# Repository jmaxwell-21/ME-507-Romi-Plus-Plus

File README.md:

# ME 507 Romi++ Project

Design repository for Romi++, a self-balancing differential drive robot developed for Cal Poly's ME 507 Mechanical Control Systems Design class.

## Documentation

[View the complete Doxygen code documentation](https://jmaxwell-21.github.io/ME-507-Romi-Plus-Plus/)

## GitHub File Structure

- `Firmware/` - STM32CubeIDE project source code and FSM diagrams
- `Hardware/` - Mechanical and electrical design files and information
- `Media/` -  Project photos and videos
- `docs/` - Doxygen-generated HTML documentation

---

Made by Jack Maxwell  
Cal Poly | Spring 2025

# Overview

Romi++ is a two-wheeled differential drive robot with a cylindrical body. It can be remotely controlled by either a computer or the custom [Smart Knob Controller](https://github.com/Larson-Nick/SmartKnobController) built by my partner and can drive at speeds up to 1&nbsp;m/s while autonomously maintaining balance through PID control.

## See Romi++ in action!
<table>
  <tr>
    <td align="center" valign="top">
      <a href="https://youtube.com/shorts/c_1nM_AD648">
        <br>
        <strong>Official Project Demo</strong>
      </a>
      <p>Official project demo showcasing wireless two-wheeled robot with custom controller (using attachments before balance control was implemented).</p>
    </td>
    <td align="center" valign="top">
      <a href="https://youtube.com/shorts/LBDbpKdLq8A">
        <br>
        <strong>Bonus Project Demo</strong>
      </a>
      <p>Final demo with balance control enabled, allowing the robot to stay level while driving without attachments.</p>
    </td>
  </tr>
</table>

This project serves as a successor to my [Romi Line-Following Robot](https://github.com/finite-colin-machine/ME-405-Romi) project from ME 405 at Cal Poly. Unlike the original Romi, which used caster wheels for stability, Romi++ is cylindrical and free to rotate about its drive axis, requiring active balance control to remain upright.

Romi++ was my term project for the ME 507 Mechanical Control Systems Design class at Cal Poly. It was a perfect blend of the four core areas of mechatronics: mechanical design, electronics, embedded systems, and control systems. These aspects of my project are explained in more depth below.

## Mechanical Design

The main components of the robot are the 3D-printed cylindrical body, two motors with wheels, a battery compartment, and various fasteners. The motors are mounted beneath the mounting plate and screw into the cylinder sides. The battery sits in a small box beneath the mounting plate, while the electronics rest on top. Long standoffs connect both cylinder halves to the mounting plate.

All 3D-printed components were custom designed, while purchased components (motors, wheels, battery, fasteners) were integrated into the assembly. The challenge was ensuring proper fitment and mounting points for each component. I imported vendor-supplied CAD models into SolidWorks and iteratively refined the design to accommodate all components with appropriate mounting holes and clearances.

See the [Mechanical Design](Hardware/Mechanical) folder for more information on specific components.

## Electrical Design

The PCB that I designed for Romi++ was my first experience with electronics design. It took up a significant portion of the 10-week course, but it was worth it for all of the experience I gained (and the fun I had)!

The PCB has 9 main components: the power distribution system to supply various voltage levels to the system, the STM32 microcontroller to control all the components, an IMU to measure heading and pitch, 2 drivers and pin headers for the motors, a pin header for the HC-05 Bluetooth module, a pin header for the ST-Link debugger, a reset button, and a general-purpose user button. I designed the [schematic](Hardware/Electrical/PCB%20Schematic.pdf) and board layout in Fusion 360 and had it manufactured by JLCPCB.

See the [Electrical Design](Hardware/Electrical) folder for complete schematics, board layouts, and manufacturing files.

### Power Distribution

The robot is powered by a 3S LiPo battery with a nominal voltage of 11.1&nbsp;V. A [fuse](https://www.digikey.com/en/products/detail/littelfuse-inc/2920l400-15mr/6234817) and a [p-channel MOSFET](https://www.digikey.com/en/products/detail/infineon-technologies/IRF7416TRPBF/856470) are used for circuit protection, and the 11.1&nbsp;V from the battery goes to the two [motor driver](https://www.digikey.com/en/products/detail/texas-instruments/DRV8231DDAR/16184249) integrated circuits. A [buck regulator](https://www.digikey.com/en/products/detail/texas-instruments/lmr54406fdbvr/15926505) is used to drop the 11.1&nbsp;V to 5&nbsp;V and provide a smooth output for the encoders and the [HC-05](https://www.electronicwings.com/sensors-modules/bluetooth-module-hc-05-), and an [LDO regulator](https://www.digikey.com/en/products/detail/texas-instruments/TPS7A2033PDBVR/13566866?s=N4IgTCBcDaICoAUDKB2AgmADAZmwgIgEIBqASiALoC%2BQA) is used to drop the 5&nbsp;V to 3.3&nbsp;V to power the remaining integrated circuits.

### Microcontroller (MCU)

To run my code and control each peripheral, an [STM32F411CEU6 Microcontroller](https://www.digikey.com/en/products/detail/stmicroelectronics/STM32F411CEU6/4935720) is used. This 32-bit ARM Cortex-M4 MCU running at 100&nbsp;MHz provides sufficient processing power for real-time control loops while offering the necessary peripherals: I2C for the IMU, UART for Bluetooth communication, PWM timers for motor control, and encoder inputs for wheel speed measurement.

### Inertial Measurement Unit (IMU)

To provide heading (yaw) and pitch measurements for the robot's control system, the [BNO055](https://www.digikey.com/en/products/detail/bosch-sensortec/BNO055/6136301) 9-axis absolute orientation sensor is used. The heading data enables precise turning control, while the pitch angle is used by the balance controller to keep the robot upright. Communication with the microcontroller occurs over I2C, with the sensor providing orientation data at up to 100&nbsp;Hz for responsive control.

## Firmware and Controls

The firmware for Romi++ was developed in C/C++ using STM32CubeIDE. While driver implementations can be found in the [Firmware](Firmware) folder, this section focuses on the cooperative multitasking structure and Finite State Machine (FSM) control algorithms that enable the robot's movement.

The firmware uses a pseudo-cooperative multitasking framework where tasks execute sequentially in the main loop. Based on the connected controller (laptop or Smart Knob), different control tasks run in order, each completing its work before passing control to the next task.

### Bluetooth Task

When a laptop is connected, the Bluetooth task runs and decodes signals sent by the [robot controller](Firmware/Additional%20Code/Robot%20Controller.py) Python script. Based on which key is pressed, the task transitions between states that command the motors to move forward, backward, left, or right. When no keys are pressed, it returns to the STOP state. This control interface was primarily used for solo testing, while the custom controller served as the main input method.

### Balance Task

When a laptop is connected, the Balance task reads the pitch angle from the IMU and applies balance control to keep the robot upright. Because the robot is free to rotate about its drive axis, the cylindrical body tilts when the motors spin in the same direction. Without active balance control, the robot cannot drive effectively.

A PID controller compares the current pitch angle to the setpoint (0 degrees) and outputs a corrective motor effort that gets sent to the motor task. This creates a feedback loop that continuously adjusts the motors to maintain balance while driving.

The balance control toggles between IDLE and RUN states when the user button on the PCB is pressed. This allows demonstration of the robot's behavior with and without balance control enabled.

Balance control was not implemented in time for the official project demonstration, which is why an attachment was used to prevent the robot from spinning in that demo. This is also why balance control only runs while a laptop is connected and not with the Smart Knob Controller.

### Parser Task

The Parser task decodes command strings received from the Smart Knob Controller via UART IDLE-line detection with DMA reception. Commands begin with a mode character ('A', 'B', 'C', or 'D') followed by hexadecimal values for motor duty cycles or heading setpoints. The parser extracts these values and makes them available to the motor and heading control tasks.

**Supported modes:**
- **Mode A/B**: Direct motor control (M1 and M2 duty cycles)
- **Mode C**: Reserved for future use
- **Mode D**: Combined heading and motor effort control

### Heading Task

When Mode D is active (combined heading and motor control from the Smart Knob Controller), the Heading task reads the yaw angle from the IMU and controls the robot's orientation. The task tracks the robot's angular position by accumulating angle changes while handling 360-degree wraparound, creating a continuous heading reference.

A PID controller compares the current heading to the commanded setpoint and generates opposing motor efforts for differential steering. These efforts are added to any forward/backward motion commands, allowing the robot to drive while maintaining orientation.

The heading control activates only in Mode D and returns to IDLE when the controller switches modes. Pressing the user button calibrates the heading by resetting the accumulated position to match the current setpoint, which is useful for correcting drift or realigning the reference frame during operation.

### Motor Task

The Motor task serves as the central control hub that integrates commands from all other tasks and translates them into PWM signals for the motor drivers. It receives speed setpoints from either the Bluetooth or Parser tasks and uses encoder feedback to implement closed-loop speed control with PID.

The task continuously reads encoder speeds and calculates PID corrections to match the commanded wheel velocities. Crucially, it then superposes control efforts from the Heading and Balance tasks onto these base speed commands. This allows the robot to simultaneously drive at a target speed, maintain orientation, and stay upright.

The motor task transitions from IDLE to RUN whenever any input source provides non-zero commands or control efforts. Final motor efforts are clamped to safe PWM limits before being sent to the motor drivers, ensuring the robot operates within hardware constraints. This architecture makes the Motor task the final stage in a layered control system where multiple independent controllers work together to achieve complex behavior.

### Battery Check Task

The Battery Check task monitors the battery voltage through an ADC input and provides a visual warning when power drops too low. It continuously reads the analog voltage level and compares it against threshold values to protect the LiPo battery from over-discharge.

When the battery voltage drops below approximately 10.05 V (ADC value < 3300), the task activates an LED indicator and transitions to the BATTERY_LOW state. Once in this state, the LED remains on until the voltage recovers to at least 10.20 V (ADC value > 3350), at which point it turns off and returns to normal monitoring.

This design prevents the LED from flickering on and off when the battery voltage hovers near the threshold, as motor loads can cause temporary voltage dips that recover quickly. When the battery is depleted and requires charging, it must be disconnected to do so. The specific voltage thresholds are chosen to provide a safe margin above the 3 V per cell over-discharge limit (9 V total for a 3S battery).

## Project Results and Reflection

Romi++ successfully demonstrates the integration of mechanical design, electronics, embedded systems, and control systems into a fully functional balancing robot. The final system achieves autonomous balance control, precise heading tracking, and wireless operation through two independent control interfaces.

**Key achievements:**
- DFMA-driven design with standardized fasteners and single-tool access
- Custom PCB design and fabrication with successful implementation
- Multi-layered control architecture with superposed PID controllers
- Wireless control via Bluetooth for laptop and custom controller interfaces

**Challenges and lessons learned:**

Designing the PCB was a grueling task, especially with no prior experience. Over about 4 weeks, I learned about decoupling capacitors, ground planes, trace routing, and many more topics while iterating and improving my design. The end result was a board with no defects that worked perfectly on the first try, which is something I am very proud of!

With only 3 weeks to write and test the code after receiving the PCB, the project required careful prioritization of features. Before implementing balance control, I first had to ensure my robot could communicate with the Smart Knob Controller and interpret its commands for the project demo. Tuning multiple PID controllers required systematic testing documented in the [project videos](Media).

**Future improvements:**
- Enable Bluetooth connection with Xbox/PlayStation controller for more versatile and intuitive control
- Optimize PID gains for faster response and better disturbance rejection
- Create a new iteration with omnidirectional movement, jumping capabilities, and a built-in camera, similar to the [drones in Rainbow Six Siege](https://rainbowsix.fandom.com/wiki/Drone)

This project provided hands-on experience across the full mechatronics design cycle, from initial CAD modeling through PCB design to firmware development and control system tuning. Special thanks to [Nick Larson](https://github.com/Larson-Nick) for developing the Smart Knob Controller that elevated this project's user experience.

## Media Gallery
Check out the [Media folder](Media) for photos and videos of project development. Watch the [full video playlist](https://www.youtube.com/playlist?list=PLDFOiaVsUKKqYprYMNDaC-OZPWteVwOPU) to see the robot's development from first tests to final demonstration.

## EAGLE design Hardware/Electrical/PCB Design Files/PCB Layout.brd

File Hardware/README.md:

# Hardware

This folder contains all electrical and mechanical design files for the Romi++ Differential Drive Robot, including PCB schematics, board layout, manufacturing assets, and CAD models.

## Contents

### `Electrical/` – Fusion PCB design files, manufacturing exports, and board reference images

- `JLCPCB Order Info/` – Gerber files, bill of materials (BOM), and pick-and-place data for PCB fabrication, see notes for more info
- `PCB Design Files/` – Schematic (`.sch`), board layout (`.brd`), 3D model (`.step`), and full Fusion 360 project archive (`.f3z`)
- Additional Files – Reference images of the board, schematic and layout PDFs

### `Mechanical/` – SolidWorks CAD files, 3D-printable models, and robot images

- `SolidWorks 2024 Part Files/` – Native `.SLDPRT` and `.SLDASM` files, including McMaster-Carr fasteners and vendor-supplied STEP models
- `STL 3-D Print Files/` – Exported `.stl` files ready for 3D printing
- `Robot BOM.csv` - Bill of materials for the mechanical assembly, see notes for more info
- Additional Files – Images of the assembled robot and CAD assembly

---

## How to Open the Files

### SolidWorks Files

1. Launch **SolidWorks 2024** or compatible version
2. Open `.SLDASM` files from `SolidWorks 2024 Part Files/`
3. Make sure subfolders (e.g., fasteners, STEP parts) are in the same root for proper assembly resolution

### Fusion 360 Files

1. Open Fusion 360
2. Go to **File → Open**
3. Select `ME 507 Romi++.f3z` to import the PCB project including schematic and layout

---

## Notes

- Mechanical Notes
    - Components not included in BOM were provided by my instructor
    - 20  8mm M3 Screws
    - 12 10mm M3 Screws
    - 12 12mm M3 Screws
    - 44 M3 Washers (.5mm thick)
    -  8 M3 Hex Nuts
- Electrical notes
    - For the JLCPCB order, some PCB components needed to be adjusted. This consisted of rotating some parts into the correct orientation seen on my board layout. For any recreations of this project, it is highly recommended to have the manufacturer review the design for you before assembly begins.

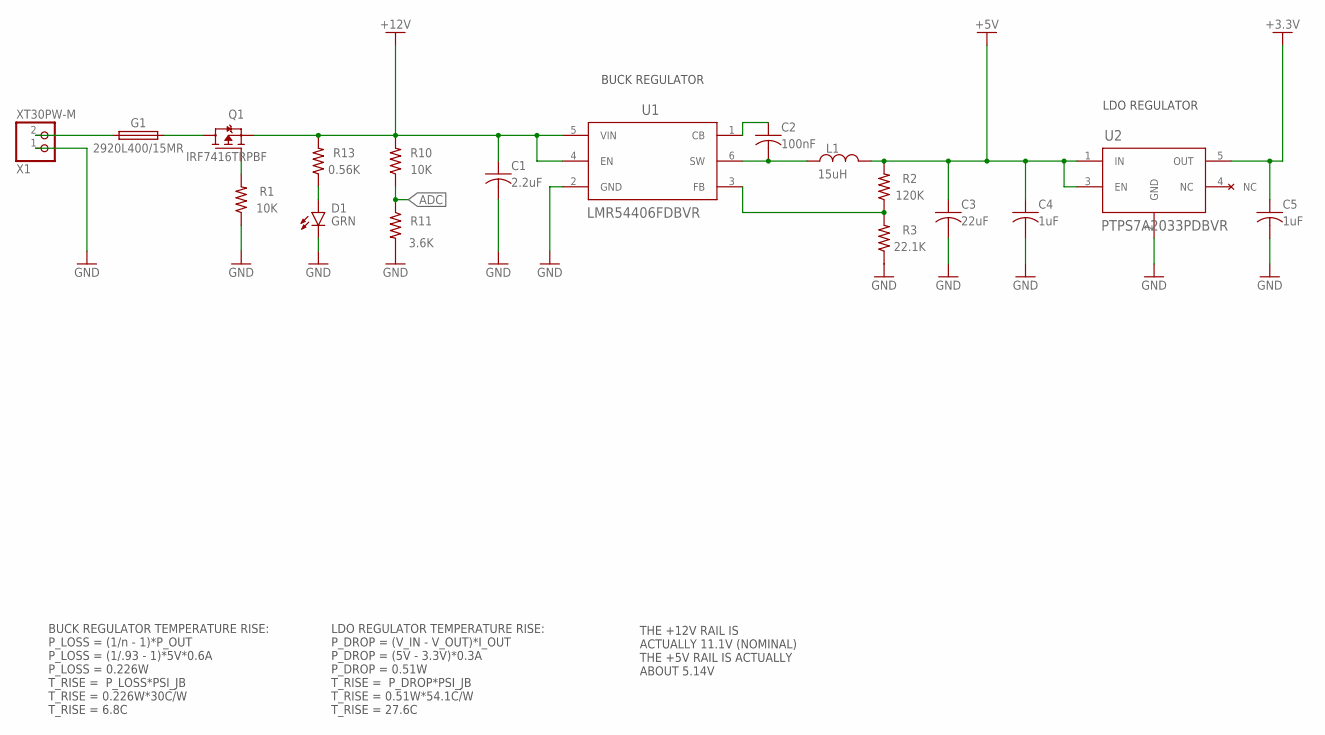
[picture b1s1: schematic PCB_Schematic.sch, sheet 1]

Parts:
C1: 2.2uF; CAPC2012X110
C2: 100nF; CAPC1608X85
C3: 22uF; CAPC3216X135
C4, C5: 1uF; CAPC2012X110
D1: GRN; LEDC2012X110N_FLAT-G
G1: 2920L400/15MR; FUSC7351X160
L1: 15uH; IND_XGL4040_COC
Q1: IRF7416TRPBF; SO-8
R1, R10: 10K; RESC2012X65
R2: 120K; RESC2012X65
R3: 22.1K; RESC2012X65
R11: 3.6K; RESC1608X60
R13: 0.56K; RESC3224X71
U1: LMR54406FDBVR; LMR54406DBVR_TEX
U2: PTPS7A2033PDBVR; DBV0005A-MFG
X1: XT30PW-M

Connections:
+3.3V: C5.1, U2.5 (OUT); also elsewhere on the board
+5V: C3.1, C4.1, L1.2, R2.2, U2.1 (IN), U2.3 (EN); also elsewhere on the board
+12V: C1.1, Q1.1 (S), Q1.2 (S), Q1.3 (S), R10.2, R13.2, U1.4 (EN), U1.5 (VIN); also elsewhere on the board
ADC: R10.1, R11.1; also elsewhere on the board
GND: C1.2, C3.2, C4.2, C5.2, D1.C, R1.1, R3.1, R11.2, U1.2 (GND), U2.2 (GND), X1.1; also elsewhere on the board
unnamed: C2.1, U1.1 (CB)
unnamed: C2.2, L1.1, U1.6 (SW)
unnamed: Q1.4 (G), R1.2
unnamed: R2.1, R3.2, U1.3 (FB)
unnamed: G1.1, X1.2
unnamed: G1.2, Q1.5 (D), Q1.6 (D), Q1.7 (D), Q1.8 (D)
unnamed: D1.A, R13.1

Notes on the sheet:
BUCK REGULATOR
LDO REGULATOR
BUCK REGULATOR TEMPERATURE RISE: P_LOSS = (1/n - 1)*P_OUT P_LOSS = (1/.93 - 1)*5V*0.6A P_LOSS = 0.226W T_RISE = P_LOSS*PSI_JB T_RISE = 0.226W*30C/W T_RISE = 6.8C
LDO REGULATOR TEMPERATURE RISE: P_DROP = (V_IN - V_OUT)*I_OUT P_DROP = (5V - 3.3V)*0.3A P_DROP = 0.51W T_RISE = P_DROP*PSI_JB T_RISE = 0.51W*54.1C/W T_RISE = 27.6C
THE +12V RAIL IS ACTUALLY 11.1V (NOMINAL) THE +5V RAIL IS ACTUALLY ABOUT 5.14V

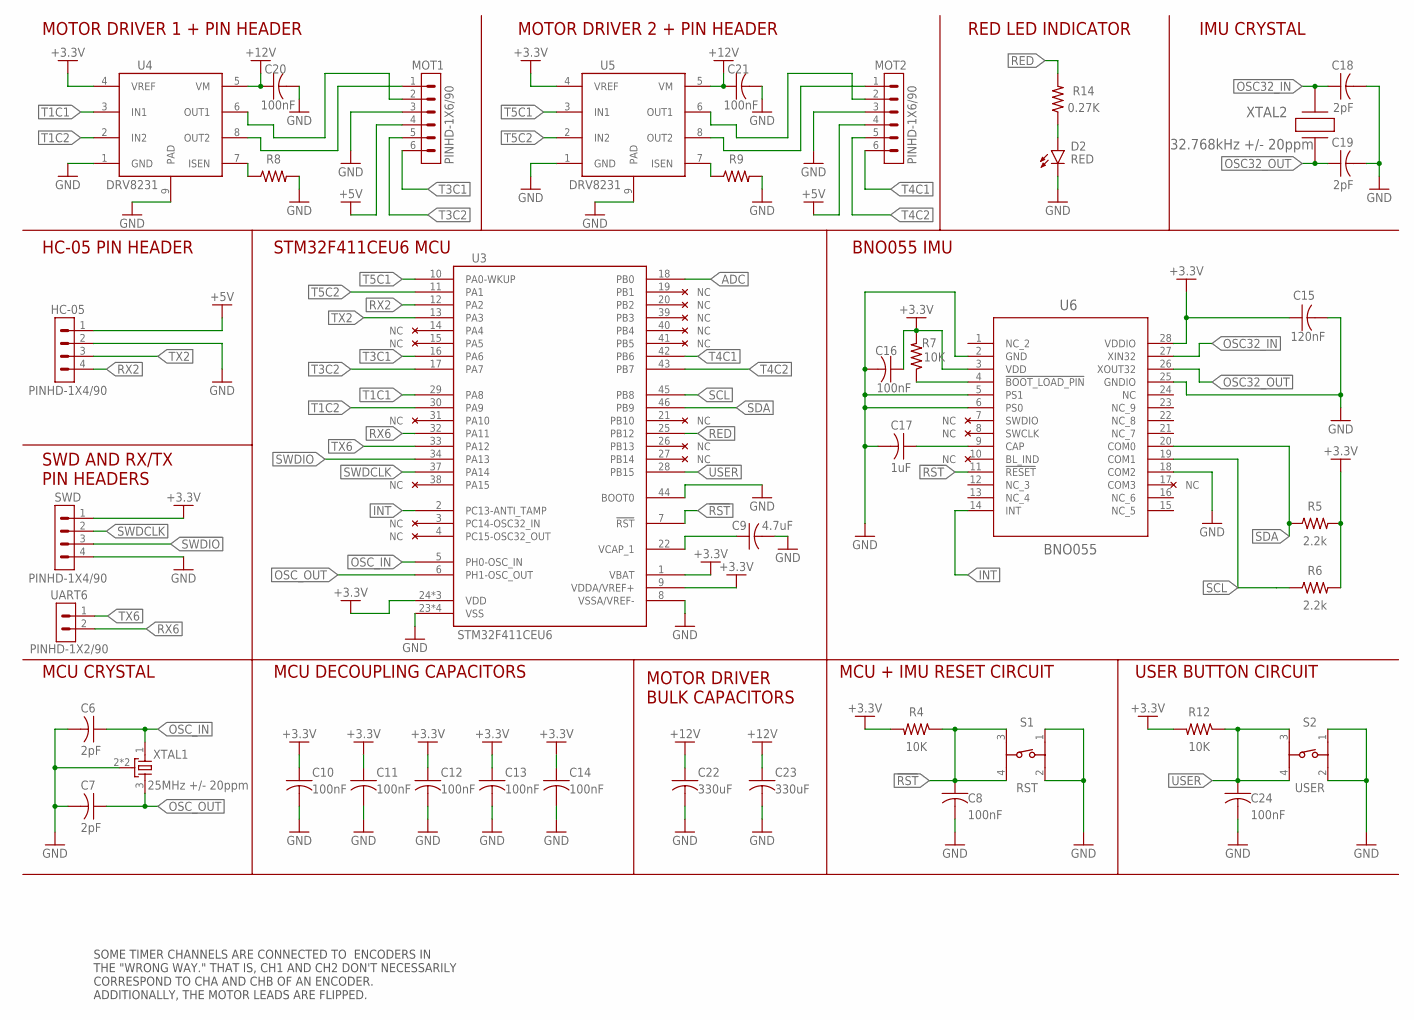
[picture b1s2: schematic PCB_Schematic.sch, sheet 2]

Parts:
C6, C7, C18, C19: 2pF; CAPC1005X60
C8, C10, C11, C12, C13, C14, C16, C24: 100nF; CAPC1005X60
C9: 4.7uF; CAPC3216X135
C15: 120nF; CAPC1608X85
C17: 1uF; CAPC1608X85
C20, C21: 100nF; CAPC1608X85
C22, C23: 330uF; CAPAE660X800N
D2: RED; LEDC2012X110N_FLAT-R
HC-05: PINHD-1X4/90; 1X04/90
MOT1, MOT2: PINHD-1X6/90; 1X06/90
R4, R7, R12: 10K; RESC2012X65
R5, R6: 2.2k; RESC1608X60
R8, R9: R-US_CHIP-1206(3216-METRIC); RESC3216X70
R14: 0.27K; RESC2012X65
S1: RST; 430481035816
S2: USER; 430481035816
SWD: PINHD-1X4/90; 1X04/90
U3: STM32F411CEU6; QFN50P700X700X100-48N
U4, U5: DRV8231; DRV8231DDAR
U6: BNO055; QFN_BNO055_BOS
UART6: PINHD-1X2/90; 1X02/90
XTAL1: 25MHz +/- 20ppm; OSCCC200X160X50N
XTAL2: 32.768kHz +/- 20ppm; CHIP_NX3215S_NDK

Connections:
!RST!: C8.1, R4.1, S1.3, S1.4, U3.7 (!RST), U6.11 (!RESET)
+3.3V: C10.1, C11.1, C12.1, C13.1, C14.1, C15.1, C16.1, R4.2, R5.2, R6.2, R7.2, R12.2, SWD.1, U3.1 (VBAT), U3.9 (VDDA/VREF+), U3.24 (VDD), U3.36 (VDD), U3.48 (VDD), U4.4 (VREF), U5.4 (VREF), U6.3 (VDD), U6.28 (VDDIO); also elsewhere on the board
+5V: HC-05.1, MOT1.4, MOT2.4; also elsewhere on the board
+12V: C20.1, C21.1, C22.1, C23.1, U4.5 (VM), U5.5 (VM); also elsewhere on the board
ADC: U3.18 (PB0); also elsewhere on the board
GND: C6.2, C7.2, C8.2, C9.2, C10.2, C11.2, C12.2, C13.2, C14.2, C15.2, C16.2, C17.2, C18.2, C19.2, C20.2, C21.2, C22.2, C23.2, C24.2, D2.C, HC-05.2, MOT1.3, MOT2.3, R8.2, R9.2, S1.1, S1.2, S2.1, S2.2, SWD.4, U3.8 (VSSA/VREF-), U3.23 (VSS), U3.35 (VSS), U3.44 (BOOT0), U3.47 (VSS), U3.49 (VSS), U4.1 (GND), U4.9 (PAD), U5.1 (GND), U5.9 (PAD), U6.2 (GND), U6.5 (PS1), U6.6 (PS0), U6.18 (COM2), U6.25 (GNDIO), XTAL1.2 (GND), XTAL1.4 (GND); also elsewhere on the board
INT: U3.2 (PC13-ANTI_TAMP), U6.14 (INT)
unnamed: MOT1.2, U4.6 (OUT1)
unnamed: MOT1.1, U4.8 (OUT2)
unnamed: C17.1, U6.9 (CAP)
unnamed: R7.1, U6.4 (!BOOT_LOAD_PIN)
unnamed: R8.1, U4.7 (ISEN)
unnamed: MOT2.2, U5.6 (OUT1)
unnamed: MOT2.1, U5.8 (OUT2)
unnamed: D2.A, R14.1
unnamed: R9.1, U5.7 (ISEN)
OSC32_IN: C18.1, U6.27 (XIN32), XTAL2.2
OSC32_OUT: C19.1, U6.26 (XOUT32), XTAL2.1
OSC_IN: C6.1, U3.5 (PH0-OSC_IN), XTAL1.1
OSC_OUT: C7.1, U3.6 (PH1-OSC_OUT), XTAL1.3 (2)
RED: R14.2, U3.25 (PB12)
RX2: HC-05.4, U3.12 (PA2)
RX6: U3.32 (PA11), UART6.2
SCL: R6.1, U3.45 (PB8), U6.19 (COM1)
SDA: R5.1, U3.46 (PB9), U6.20 (COM0)
SWDCLK: SWD.2, U3.37 (PA14)
SWDIO: SWD.3, U3.34 (PA13)
T1C1: U3.29 (PA8), U4.3 (IN1)
T1C2: U3.30 (PA9), U4.2 (IN2)
T3C1: MOT1.6, U3.16 (PA6)
T3C2: MOT1.5, U3.17 (PA7)
T4C1: MOT2.6, U3.42 (PB6)
T4C2: MOT2.5, U3.43 (PB7)
T5C1: U3.10 (PA0-WKUP), U5.3 (IN1)
T5C2: U3.11 (PA1), U5.2 (IN2)
TX2: HC-05.3, U3.13 (PA3)
TX6: U3.33 (PA12), UART6.1
USER: C24.1, R12.1, S2.3, S2.4, U3.28 (PB15)
VCAP_1: C9.1, U3.22 (VCAP_1)

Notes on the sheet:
MOTOR DRIVER 1 + PIN HEADER
MOTOR DRIVER 2 + PIN HEADER
IMU CRYSTAL
BNO055 IMU
MCU + IMU RESET CIRCUIT
MCU DECOUPLING CAPACITORS
STM32F411CEU6 MCU
HC-05 PIN HEADER
SWD AND RX/TX PIN HEADERS
MCU CRYSTAL
MOTOR DRIVER BULK CAPACITORS
USER BUTTON CIRCUIT
RED LED INDICATOR
SOME TIMER CHANNELS ARE CONNECTED TO ENCODERS IN THE "WRONG WAY." THAT IS, CH1 AND CH2 DON'T NECESSARILY CORRESPOND TO CHA AND CHB OF AN ENCODER. ADDITIONALLY, THE MOTOR LEADS ARE FLIPPED.

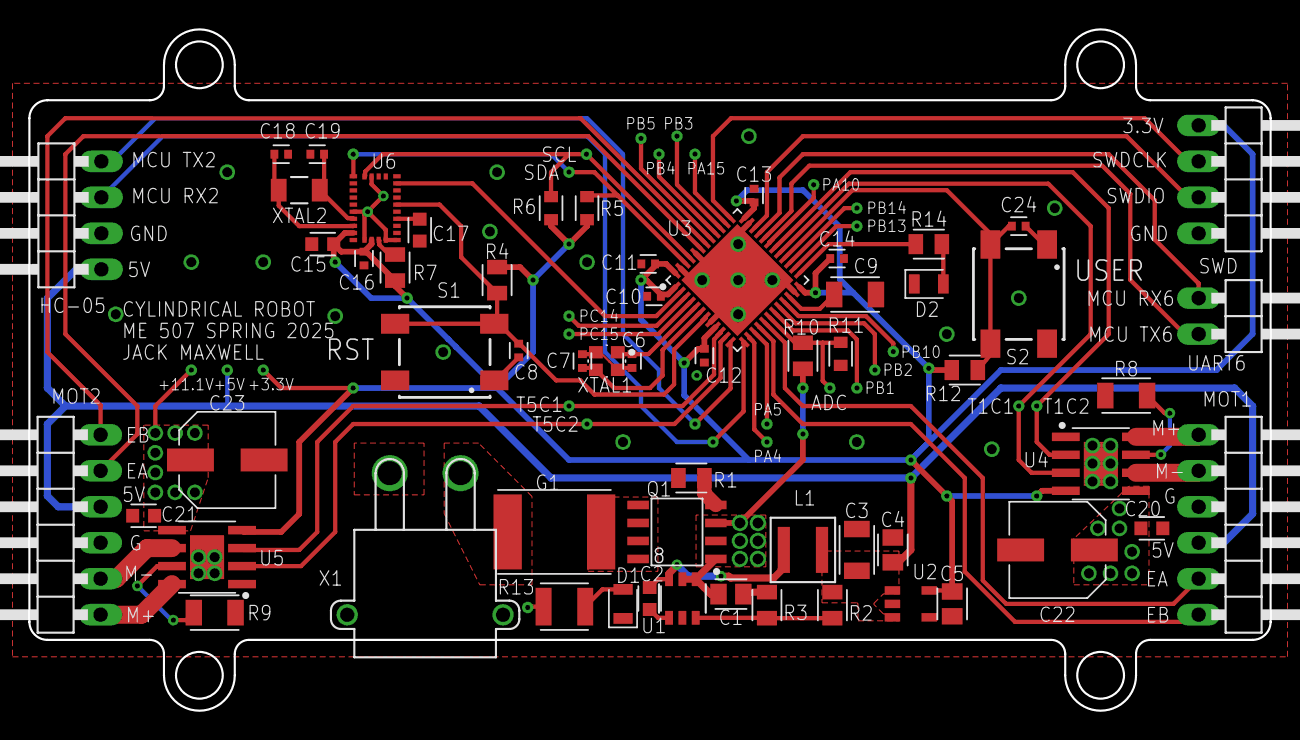
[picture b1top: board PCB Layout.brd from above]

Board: 2 copper layers, 87.6 x 48.1 mm, 59 parts (0 on the bottom side), 46 nets.

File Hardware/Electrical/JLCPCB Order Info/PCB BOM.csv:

Comment,Designator,Footprint,JLCPCB Part #
25MHz Crystal,XTAL1,SMD2016-4P,C19711739
32.768kHz Crystal,XTAL2,SMD3215-2P,C156244
Tactile Switch,"S1, S2",SMD 6x6mm 3.5mm,C5183855
8A Trip Fuse,G1,2920,C720182
30V 10A PMOSFET,Q1,SOIC-8,C3000
600mA Step-Down Regulator,U1,SOT-23-6,C3193129
300mA LDO Regulator,U2,SOT-23-5,C2862740
STM32F411CEU6 MCU,U3,UFQFPN-48(7x7),C60420
Brushed DC Motor Driver,"U4, U5",SOPowerPAD(DDA)-8,C5218850
BNO055 IMU,U6,LGA-28(3.8x5.2),C93216
10kΩ,"R1, R4, R7, R10, R12",0805,C84376
118kΩ,R2,0805,C103948
22.1kΩ,R3,0805,C204311
2.2kΩ,"R5, R6",0603,C114662
"100mΩ, 0.5W","R8, R9",1206,C346763
3.6kΩ,R11,0603,C137729
"560Ω, 0.5W",R13,1210,C3000758
"270Ω, .125W",R14,0805,C485675
"2.2uF, 25V, X7R",C1,0805,C19110
".1uF, 16V, X7R",C2,0603,C66501
"22uF, 10V, X7R",C3,1206,C909845
"1uF, 10V, X7R","C4, C5, C17",0805,C1712
"2pF, 10V, X8R","C6, C7, C18, C19",0402,C161316
"100nF, 10V, X7R","C8, C10-14, C16, C24",0402,C1525
"4.7uF, 10V, X7R",C9,1206,C1872
"120nF, 10V, X7R",C15,0603,C107063
"100nF, 25V, X7R","C20, C21",0603,C1590
"330uF, 25V, AEC-Q200","C22, C23","SMD,D6.3xL7.7mm",C2980171
15uH,L1,1616,C3911667
20mA 2.1V Green,D1,0805,C5875740
5mA 2.0V Red,D2,0805,C5349939

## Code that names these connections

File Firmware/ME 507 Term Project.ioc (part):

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Mcu.Name=STM32F411C(C-E)Ux
Mcu.Package=UFQFPN48
Mcu.UserName=STM32F411CEUx
PA0-WKUP.Signal=S_TIM5_CH1
PA1.Signal=S_TIM5_CH2
PA11.Mode=Asynchronous
PA11.Signal=USART6_TX
PA12.Mode=Asynchronous
PA12.Signal=USART6_RX
PA13.Mode=Trace_Asynchronous_SW
PA13.Signal=SYS_JTMS-SWDIO
PA14.Mode=Trace_Asynchronous_SW
PA14.Signal=SYS_JTCK-SWCLK
PA2.Mode=Asynchronous
PA2.Signal=USART2_TX
PA3.Mode=Asynchronous
PA3.Signal=USART2_RX
PA5.Signal=S_TIM2_CH1_ETR
PA6.Signal=S_TIM3_CH1
PA7.Signal=S_TIM3_CH2
PA8.Signal=S_TIM1_CH1
PA9.Signal=S_TIM1_CH2
PB0.Signal=ADCx_IN8
PB12.Signal=GPIO_Output
PB15.GPIOParameters=GPIO_ModeDefaultEXTI
PB15.GPIO_ModeDefaultEXTI=GPIO_MODE_IT_FALLING
PB15.Signal=GPXTI15
PB3.Mode=Trace_Asynchronous_SW
PB3.Signal=SYS_JTDO-SWO
PB6.Signal=S_TIM4_CH1
PB7.Signal=S_TIM4_CH2
PB8.Mode=I2C
PB8.Signal=I2C1_SCL
PB9.Mode=I2C
PB9.Signal=I2C1_SDA
PH0\ -\ OSC_IN.Mode=HSE-External-Oscillator
PH0\ -\ OSC_IN.Signal=RCC_OSC_IN
PH1\ -\ OSC_OUT.Mode=HSE-External-Oscillator
PH1\ -\ OSC_OUT.Signal=RCC_OSC_OUT
RCC.HSE_VALUE=25000000
RCC.SYSCLKFreq_VALUE=96000000
RCC.SYSCLKSource=RCC_SYSCLKSOURCE_PLLCLK
board=custom

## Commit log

2025-06-14 Initial commit: STM32 project setup and Doxygen documentation
2025-06-14 Fixed GitHub Pages: added .nojekyll
2025-06-14 Fix folder case: rename Docs to docs for GitHub Pages
2025-06-14 Add Doxygen documentation to docs folder
2025-06-14 Addded Firmware README with STM32 Project Details
2025-06-14 Created README.md for Firmware folder with information for the STM32 Project
2025-06-14 Updated README.md with better instructions
2025-06-16 Added robot BOM, hardware README; update firmware README; removed unused fastener
2025-06-16 Re-worded Hardware README and changed some file/folder names for clarity
2025-10-17 Add remaining files and finished project documentation
2026-03-08 Update README.md
    Fix README grammar

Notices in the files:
parts and their libraries:
430481035816: Copyright: Würth Elektronik
COPYRIGHT: Copyright (C) 2025 Ultra Librarian. All rights reserved.
